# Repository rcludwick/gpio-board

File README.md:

# gpio-board Raspberry Pi GPIO Board

The kicad design files are in kicad.

The python source for maniuplating the LEDS are in src.  

### gpio board in action

### Board rendering

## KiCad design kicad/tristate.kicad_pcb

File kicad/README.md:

### The gpio board

The gpio board was created using KiCad 5.  (And should be renamed to something else)

### OSH Park

To make a board, use OSH Park.  Upload the `tristate.kicad_pcb` file.

### Parts

The connector is a .1" 2x5 connector.  Similar to this: 
https://ae01.alicdn.com/kf/HTB14E6sJFXXXXaIXVXXq6xXFXXXK/10PCS-2x5-2-54mm-10Pin-Double-Row-Female-Straight-Header-Pitch-Socket-Pin-Strip-Connectors.jpg

While the schematic notes 200 ohm resistors, these should be paired to the LED that you're using.  Eg

    A Diode with a 1.9V forward voltage should use around a 1400 ohm resitor for a 1ma current.  
    
    (3.3v - 1.9v) / .001 mA = 1400ohm.

These are 1206 surface mounts, and can be bought from Digikey, Mouser, Aliexpress, Banggood.

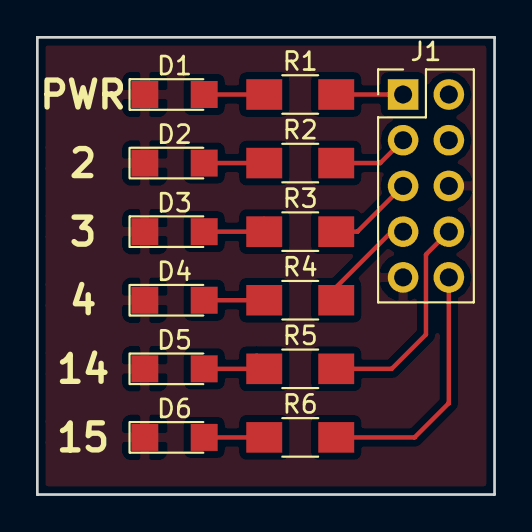
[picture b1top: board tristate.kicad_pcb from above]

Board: 2 copper layers, 25.4 x 25.4 mm, 14 parts (1 on the bottom side), 13 nets.

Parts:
D1: Red; LED_1206
D2, D3, D4, D5, D6: Blue; LED_1206
J1: CONN_02X05; Pin_Header_Straight_2x05_Pitch2.54mm
LOGO: LOGO
R1, R2, R3, R4, R5, R6: 200; R_1206_HandSoldering

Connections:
/3V3: J1.1, R1.2
/GPIO2: J1.3, R2.2
/GPIO3: J1.5, R3.2
/GPIO4: J1.7, R4.2
/GPIO14: J1.8, R5.2
/GPIO15: J1.10, R6.2
GND: D1.1, D2.1, D3.1, D4.1, D5.1, D6.1, J1.6, J1.9
unnamed: D1.2, R1.1
unnamed: D2.2, R2.1
unnamed: D3.2, R3.1
unnamed: D4.2, R4.1
unnamed: D5.2, R5.1
unnamed: D6.2, R6.1

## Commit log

2018-05-03 Moved things around. Added README.md.
2018-05-03 Updates.
    Added KiCad Board
    Moved software into src.
2018-05-03 Added image
